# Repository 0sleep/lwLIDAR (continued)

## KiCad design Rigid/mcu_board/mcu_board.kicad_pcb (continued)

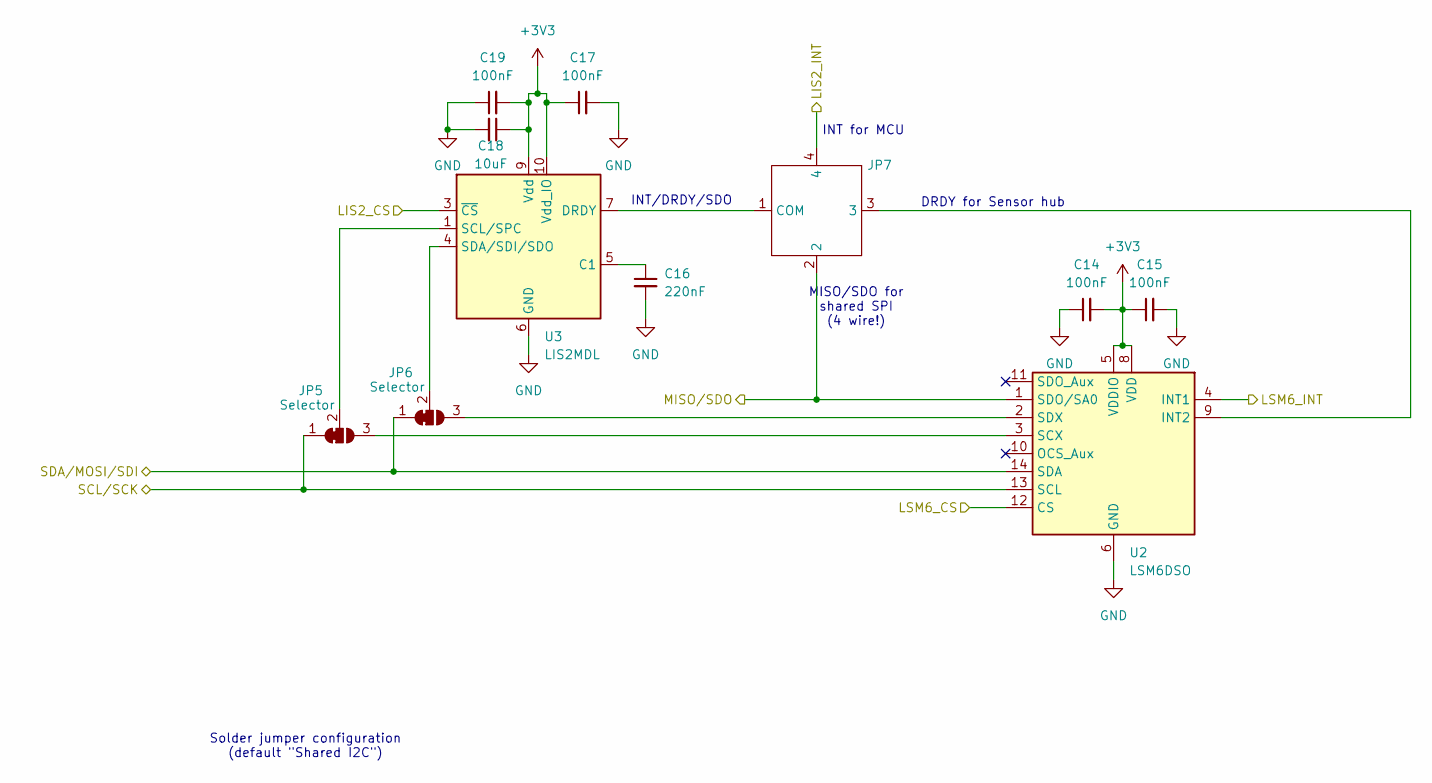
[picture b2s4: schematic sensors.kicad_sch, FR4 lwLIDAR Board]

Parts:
C14, C15, C17, C19: 100nF; C_0603_1608Metric_Pad1.08x0.95mm_HandSolder
C16: 220nF; C_0603_1608Metric_Pad1.08x0.95mm_HandSolder
C18: 10uF; C_0603_1608Metric_Pad1.08x0.95mm_HandSolder
JP5, JP6: Selector; SolderJumper-3_P1.3mm_Bridged12_RoundedPad1.0x1.5mm_NumberL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
JP7: 3waysel_default_4
U2: LSM6DSO; LGA-14_3x2.5mm_P0.5mm_LayoutBorder3x4y
U3: LIS2MDL; LGA-12_2x2mm_P0.5mm

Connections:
+3V3: C14.2, C15.1, C17.1, C18.1, C19.2, U2.5 (VDDIO), U2.8 (VDD), U3.9 (Vdd), U3.10 (Vdd_IO); also elsewhere on the board
/FSPICLK: JP5.1 (A), U2.13 (SCL); also elsewhere on the board
/FSPICS: U2.12 (CS); also elsewhere on the board
/FSPID: JP6.1 (A), U2.14 (SDA); also elsewhere on the board
/FSPIQ: JP7.2, U2.1 (SDO/SA0); also elsewhere on the board
/LIS2CS: U3.3 (~CS); also elsewhere on the board
/LIS2_INT: JP7.4; also elsewhere on the board
/LSM6_INT: U2.4 (INT1); also elsewhere on the board
GND: C14.1, C15.2, C16.2, C17.2, C18.2, C19.1, U2.6 (GND), U2.7 (GND), U3.6 (GND), U3.8 (GND); also elsewhere on the board
unnamed: JP5.3 (B), U2.3 (SCX)
unnamed: JP5.2 (C), U3.1 (SCL/SPC)
unnamed: JP6.3 (B), U2.2 (SDX)
unnamed: JP6.2 (C), U3.4 (SDA/SDI/SDO)
unnamed: JP7.1 (COM), U3.7 (DRDY)
unnamed: JP7.3, U2.9 (INT2)
unnamed: C16.1, U3.5 (C1)

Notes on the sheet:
MISO/SDO for shared SPI (4 wire!)
INT for MCU
DRDY for Sensor hub
Solder jumper configuration (default "Shared I2C")
INT/DRDY/SDO

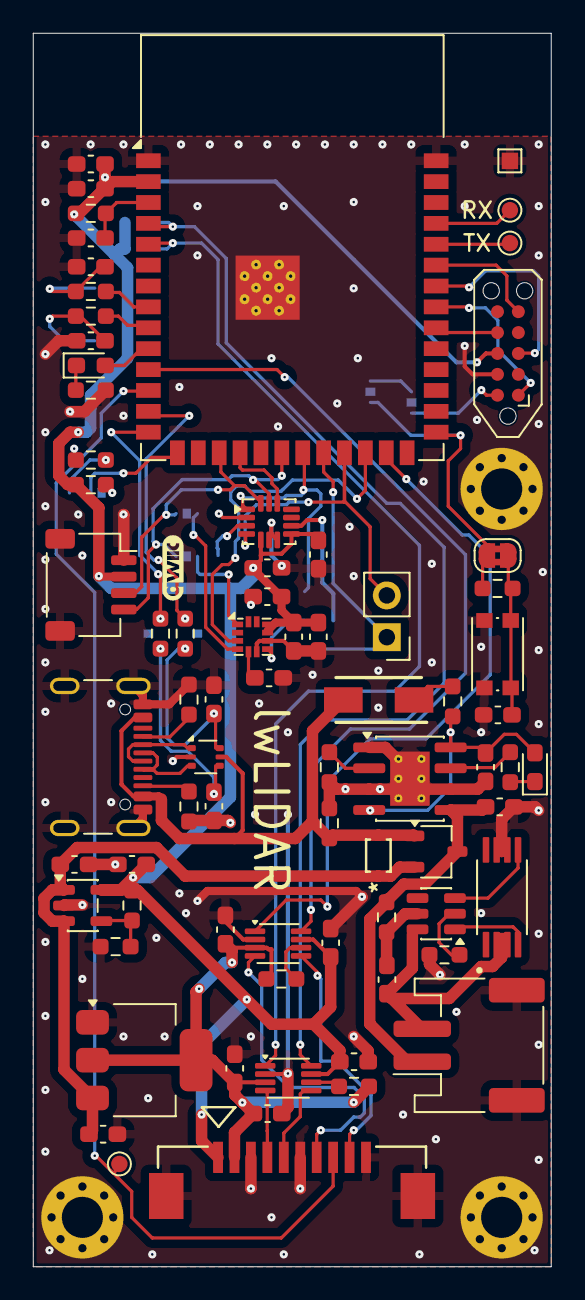
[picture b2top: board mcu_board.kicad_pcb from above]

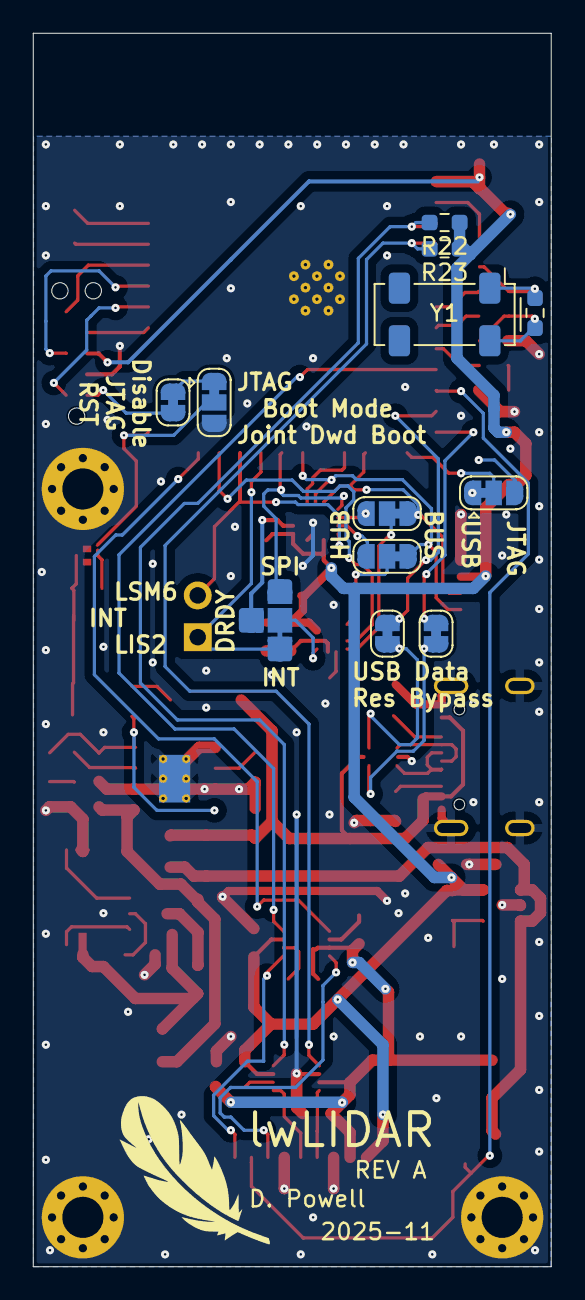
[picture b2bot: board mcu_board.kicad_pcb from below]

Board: 2 copper layers, 31.5 x 75.0 mm, 89 parts (12 on the bottom side), 70 nets.

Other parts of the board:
RX: TestPoint; TestPoint_Pad_D1.0mm
TX: TestPoint; TestPoint_Pad_D1.0mm

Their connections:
UART_RX: RX.1; also elsewhere on the board
UART_TX: TX.1; also elsewhere on the board

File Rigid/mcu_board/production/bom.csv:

Designator,Footprint,Quantity,Value,LCSC Part #
"C1, C10, C13, C22, C23, C24, C25",0603,7,0.1uF,
"C11, C12, R12, R22, R23",0603,5,DNP,
"C14, C15, C17, C19, C4, C6",0603,6,100nF,
C16,0603,1,220nF,
"C18, C2, C3, C5",0603,4,10uF,
"C20, C21",0603,2,12pf NC,
C7,0603,1,100uF,
C8,0603,1,1uF,
C9,0603,1,22uF,
"D1, D3",0603,2,LED,
D2,DIO_RB500V_ROM,1,RB551VM-30,
D4,DIOM5227X270N,1,SS14,
J1,JST_PH_S2B-PH-SM4-TB_1x02-1MP_P2.00mm_Horizontal,1,Conn_01x02_MountingPin,
J2,USB_C_Receptacle_GCT_USB4105-xx-A_16P_TopMnt_Horizontal,1,USB_C_Receptacle_USB2.0_16P,
J4,CON_522071060_MOL,1,Molex 522071060,
J5,JST_SH_SM04B-SRSS-TB_1x04-1MP_P1.00mm_Horizontal,1,QUIIC connector,
J6,PinHeader_1x02_P2.54mm_Vertical,1,Conn_01x02,
"MH1, MH2, MH3",MountingHole_2.5mm_Pad_Via,3,Conn_01x01,
Q1,SOP65P640X120-8N,1,FS8205A,
Q2,TSOT-23,1,DMP1045U,
"R1, R2",0603,2,5.1k,
"R10, R11",0603,2,0R,
"R13, R14, R15, R21, R6, R7, R9",0603,7,10k,
"R16, R17, R18",0603,3,NC,
"R19, R5",0603,2,330R,
R20,0603,1,0.4R,
R3,0603,1,100R,
R4,0603,1,1k,
R8,0603,1,2k,
"RX, TP1, TX",TestPoint_Pad_D1.0mm,3,TestPoint,
R_PROG1,0603,1,1.2k,
SW1,SW_Push_1P1T_NO_CK_KMR2,1,SW_Push,
TP4,TestPoint_Pad_1.0x1.0mm,1,TestPoint,
U1,ESP32-S3-WROOM-1,1,ESP32-S3-WROOM-1,
"U10, U8",VSSOP-8_2.3x2mm_P0.5mm,2,TXS0102DCU,
U2,LGA-14_3x2.5mm_P0.5mm_LayoutBorder3x4y,1,LSM6DSO,
U3,LGA-12_2x2mm_P0.5mm,1,LIS2MDL,
U4,SOT-23-6,1,DW01A,
U5,SOIC-8-1EP_3.9x4.9mm_P1.27mm_EP2.41x3.3mm_ThermalVias,1,TP4056-42-ESOP8,
U6,SOT-223-3_TabPin2,1,LD1117S18TR_SOT223,
U7,SOT-23-5,1,TLV75801PDBV,
U9,SOT-666,1,USBLC6-2P6,
Y1,Crystal_SMD_SeikoEpson_MC306-4Pin_8.0x3.2mm,1,NC,

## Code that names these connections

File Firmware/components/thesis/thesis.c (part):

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		printf("vl53l8cx_set_resolution failed, status %u\n", err);
		return -1;
	}
  //TODO probably obsolete due to SYNC pin
	err = vl53l8cx_set_ranging_frequency_hz(&vl_config[sensor_num], 20);
  if (err) {
		printf("vl53l8cx_set_ranging_frequency failed, status %u\n", err);
		return -1;
  }
  //Enable SYNC pin
  err = vl53l8cx_set_external_sync_pin_enable(&vl_config[sensor_num], 1);
  if (err) {
		printf("vl53l8cx_set_external_sync_pin_enable failed, status %u\n", err);
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  gpio_config_t int_conf = {
    .intr_type = GPIO_INTR_POSEDGE,
    .mode = GPIO_MODE_INPUT,
    .pin_bit_mask = (1ULL << INT_PIN),
    .pull_down_en = GPIO_PULLDOWN_DISABLE,
    .pull_up_en = GPIO_PULLUP_DISABLE,
  };
  gpio_config(&int_conf);
  gpio_install_isr_service(0);
  gpio_isr_handler_add(INT_PIN, int_isr, NULL);
  //Set up SYNC pin
  gpio_reset_pin(VL53_SYNC_PIN);
  gpio_set_direction(VL53_SYNC_PIN, GPIO_MODE_OUTPUT);
  //Set up I2C
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  struct comms_queue_item smsg;
  smsg.type = COMMS_QUEUE_ITEM_TYPE_STATS;
  //LED SETUP
  gpio_set_direction(LED_PIN, GPIO_MODE_OUTPUT);
  //LED ON
  gpio_set_level(LED_PIN, 1);
  //wait, to give me enough time between plugging in and opening monitor (or re-flashing)
  //as I need to hard-reset the sensors
  //TODO remove, obsolete
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  vTaskDelay(pdMS_TO_TICKS(100));
  printf("END DELAY\n");
  //LED OFF
  gpio_set_level(LED_PIN, 0);
  init_all();
  //TODO check if these are at all required
  vl53l8cx_start_ranging(&vl_config[0]);
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  vTaskDelay(pdMS_TO_TICKS(100));
  last_wake = xTaskGetTickCount();
  //LED ON
  gpio_set_level(LED_PIN, 1);
  while (true) {
    //Limit loop rate to max frequency
    vTaskDelayUntil(&last_wake, loop_max_frequency);
    //Flick SYNC pin
    gpio_set_level(VL53_SYNC_PIN, 1);
    vTaskDelay(pdMS_TO_TICKS(1));
    gpio_set_level(VL53_SYNC_PIN, 0);
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        }
      }
    }
    //Wait a little bit before flicking the SYNC pin. It seems to kill the last sensor otherwise
    vTaskDelay(pdMS_TO_TICKS(10));
  }
}
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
